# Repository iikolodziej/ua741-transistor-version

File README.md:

# ua741-transistor-version
This is an application of the UA741 integrated circuit implemented with transistors.

## Introduction
Haven't you always wanted to create an integrated circuit from scratch?<br /> 
See what's inside? <br /> 
How it works? <br /> 
What is it made of?<br /> 
I do! <br /> 
And that's why I reproduced a popular integrated circuit that is used in many applications, and at the same time not very complicated and easy to test.<br /> 

### Tools and others

## Gallery

Schematic and board design created in Autodesk Eagle:

<br /> 

Self made pcb:

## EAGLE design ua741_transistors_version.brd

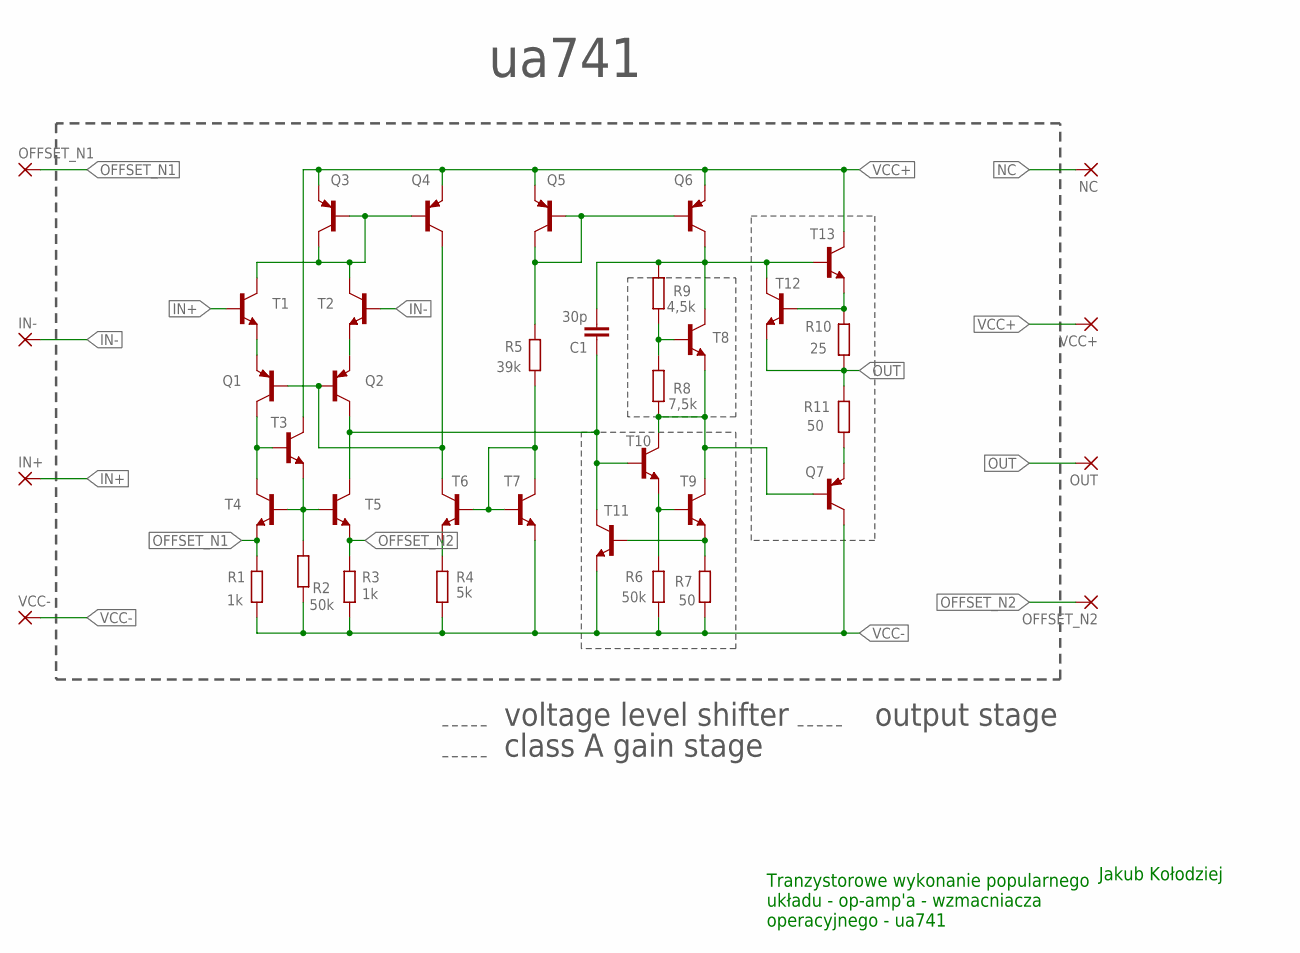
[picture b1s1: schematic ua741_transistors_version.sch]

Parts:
C1: 30p; C025-025X050
IN+: 3,81/1,4
IN-: 3,81/1,4
NC: 3,81/1,4
OFFSET_N1, OFFSET_N2: 3,81/1,4
OUT: 3,81/1,4
Q1, Q2, Q3, Q4, Q5, Q6, Q7: BC557; TO92
R1, R3: 1k; 0207/7
R2, R6: 50k; 0207/7
R4: 5k; 0207/7
R5: 39k; 0207/7
R7, R11: 50; 0207/7
R8: 7,5k; 0207/7
R9: 4,5k; 0207/7
R10: 25; 0207/7
T1, T2, T3, T4, T5, T6, T7, T8, T9, T10, T11, T12, T13: BC547; TO92
VCC+: 3,81/1,4
VCC-: 3,81/1,4

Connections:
IN+: IN+.1, T1.2 (B)
IN-: IN-.1, T2.2 (B)
unnamed: Q1.2 (B), Q2.2 (B), Q4.3 (C), T6.3 (C)
unnamed: Q1.1 (E), T1.1 (E)
unnamed: Q2.1 (E), T2.1 (E)
unnamed: Q1.3 (C), T3.2 (B), T4.3 (C)
unnamed: R2.2, T3.1 (E), T4.2 (B), T5.2 (B)
unnamed: C1.1, Q2.3 (C), T5.3 (C), T10.2 (B), T11.3 (C)
unnamed: Q3.2 (B), Q3.3 (C), Q4.2 (B), T1.3 (C), T2.3 (C)
unnamed: R4.2, T6.1 (E)
unnamed: R5.1, T6.2 (B), T7.2 (B), T7.3 (C)
unnamed: R7.2, T9.1 (E), T11.2 (B)
unnamed: R6.2, T9.2 (B), T10.1 (E)
unnamed: Q7.2 (B), R8.1, T8.1 (E), T9.3 (C), T10.3 (C)
unnamed: Q7.1 (E), R11.1
unnamed: Q5.2 (B), Q5.3 (C), Q6.2 (B), R5.2
unnamed: R10.2, T12.2 (B), T13.1 (E)
unnamed: C1.2, Q6.3 (C), R9.2, T8.3 (C), T12.3 (C), T13.2 (B)
unnamed: R8.2, R9.1, T8.2 (B)
NC: NC.1
OFFSET_N1: OFFSET_N1.1, R1.2, T4.1 (E)
OFFSET_N2: OFFSET_N2.1, R3.2, T5.1 (E)
OUT: OUT.1, R10.1, R11.2, T12.1 (E)
VCC+: Q3.1 (E), Q4.1 (E), Q5.1 (E), Q6.1 (E), T3.3 (C), T13.3 (C), VCC+.1
VCC-: Q7.3 (C), R1.1, R2.1, R3.1, R4.1, R6.1, R7.1, T7.1 (E), T11.1 (E), VCC-.1

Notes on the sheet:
ua741
voltage level shifter
class A gain stage
output stage
Jakub Kołodziej
Tranzystorowe wykonanie popularnego układu - op-amp'a - wzmacniacza operacyjnego - ua741

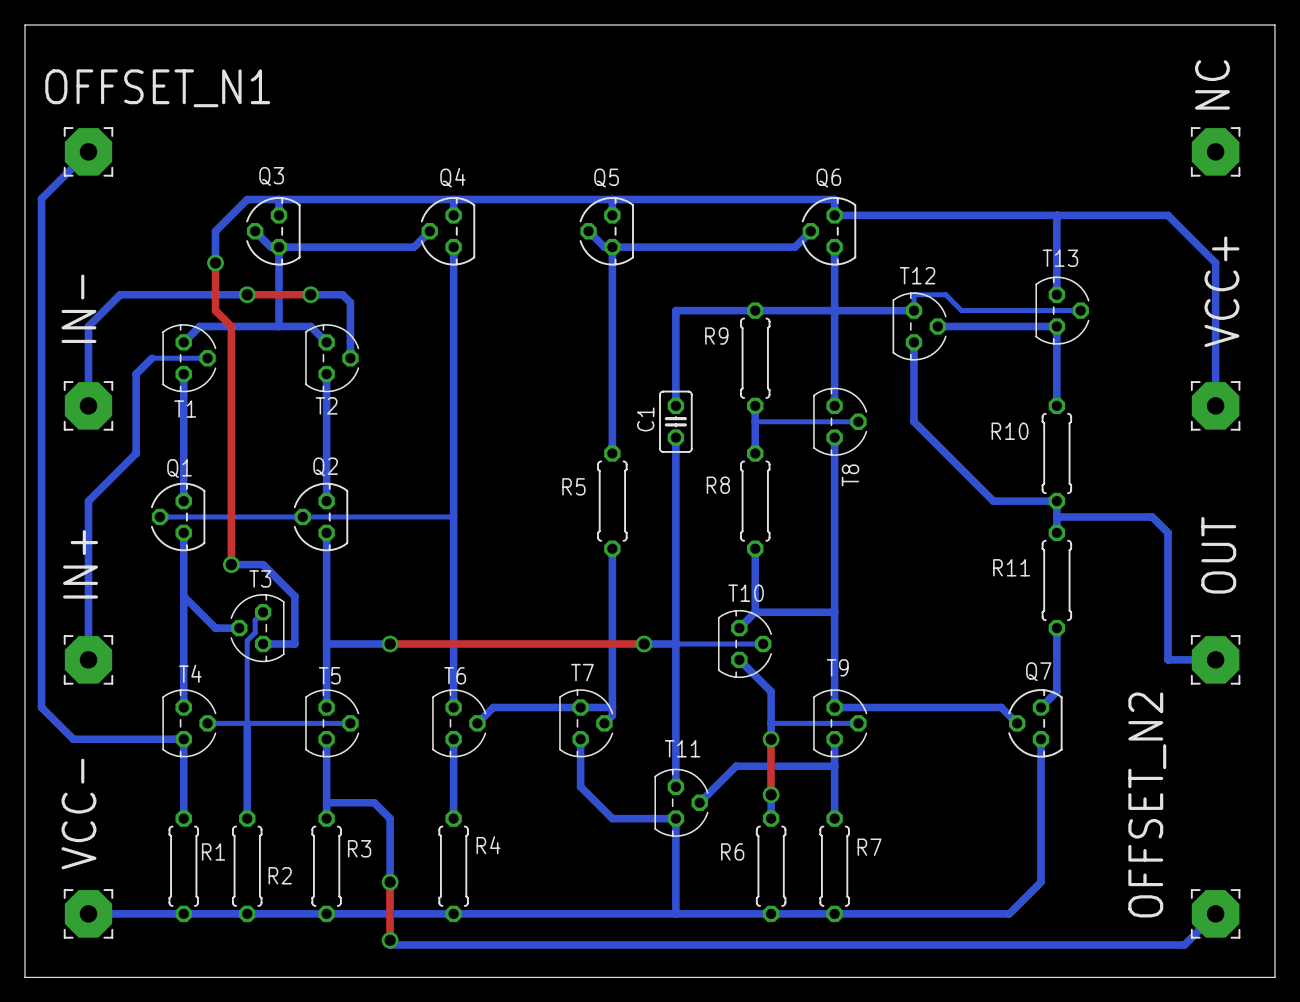
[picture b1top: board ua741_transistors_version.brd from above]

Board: 2 copper layers, 100.0 x 76.2 mm, 40 parts (0 on the bottom side), 24 nets.

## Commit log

2023-04-25 Upload .pcb and .sch files
2023-04-25 Add images of pcb and schematic
